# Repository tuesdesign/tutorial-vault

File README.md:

# Ontario Tech University Tutorial Slide Content

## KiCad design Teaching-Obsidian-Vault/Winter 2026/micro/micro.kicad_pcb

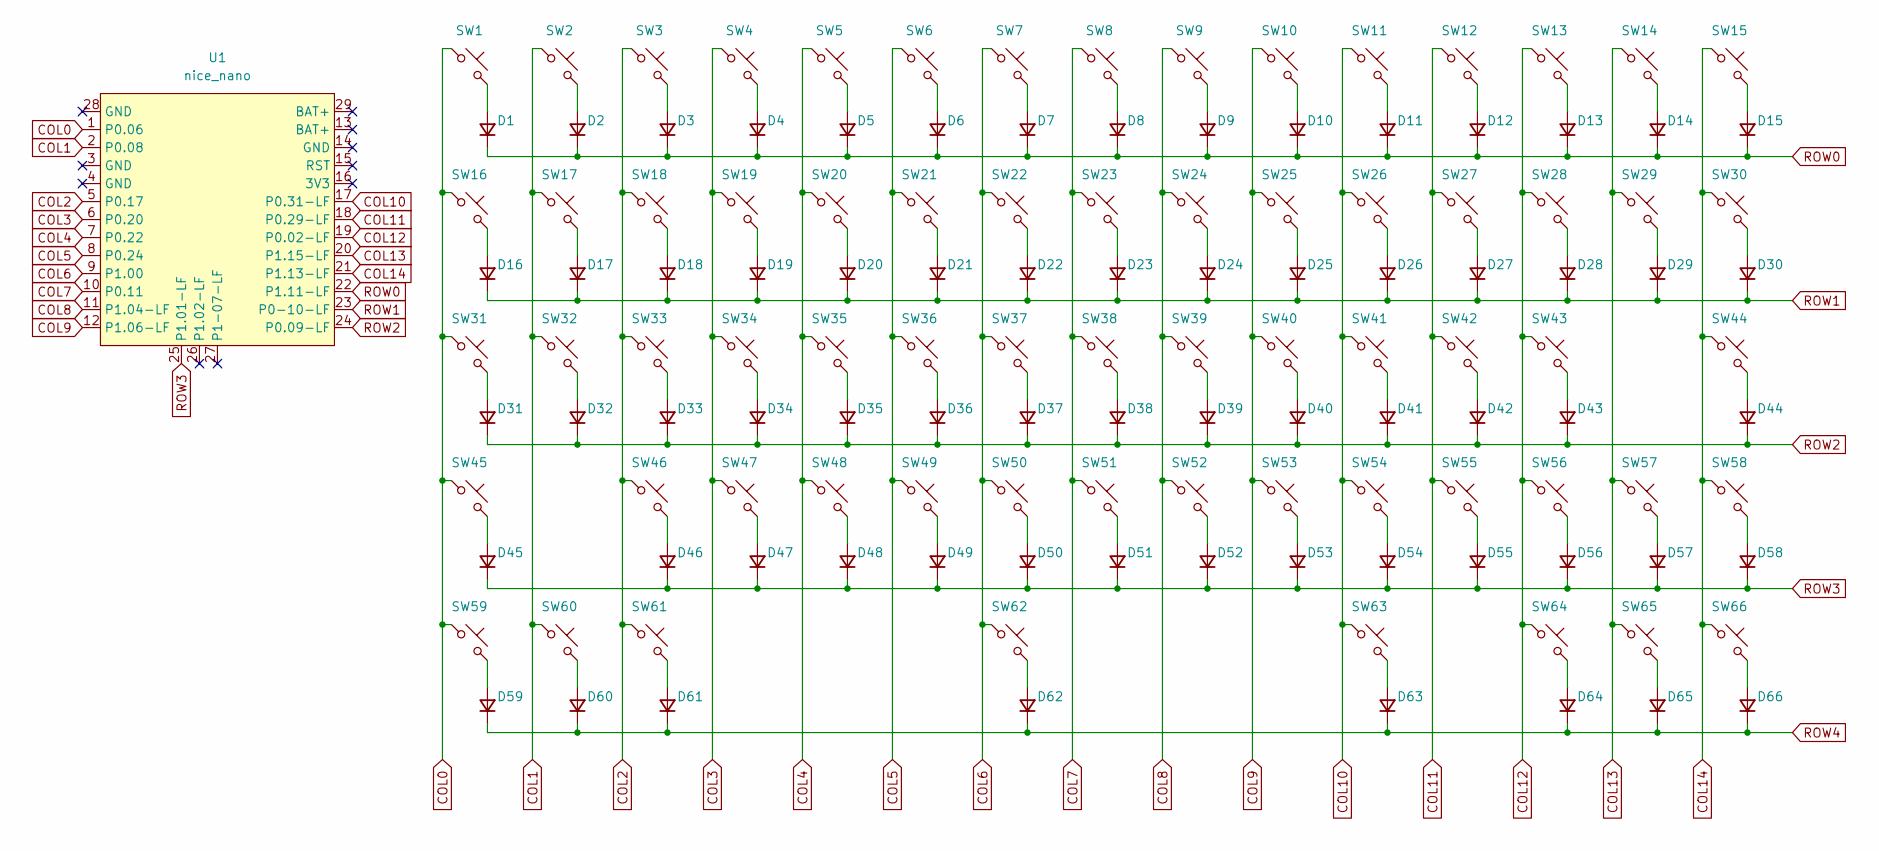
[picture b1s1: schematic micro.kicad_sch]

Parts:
D1, D2, D3, D4, D5, D6, D7, D8, D9, D10, D11, D12, D13, D14, D15, D16, D17, D18, D19, D20, D21, D22, D23, D24, D25, D26, D27, D28, D29, D30, D31, D32, D33, D34, D35, D36, D37, D38, D39, D40, D41, D42, D43, D44, D45, D46, D47, D48, D49, D50, D51, D52, D53, D54, D55, D56, D57, D58, D59, D60, D61, D62, D63, D64, D65, D66: D; D_SOD-123
SW1, SW2, SW3, SW4, SW5, SW6, SW7, SW8, SW9, SW10, SW11, SW12, SW13, SW14, SW17, SW18, SW19, SW20, SW21, SW22, SW23, SW24, SW25, SW26, SW27, SW28, SW30, SW32, SW33, SW34, SW35, SW36, SW37, SW38, SW39, SW40, SW41, SW42, SW43, SW44, SW46, SW47, SW48, SW49, SW50, SW51, SW52, SW53, SW54, SW55, SW56, SW58: SW_Push; SW_Hotswap_Kailh_Choc_V1V2_1.00u
SW15: SW_Push; SW_Hotswap_Kailh_Choc_V1V2_2.00u
SW16, SW63: SW_Push; SW_Hotswap_Kailh_Choc_V1V2_1.50u
SW29: SW_Push; SW_Hotswap_Kailh_Choc_V1_ISOEnter_90deg
SW31: SW_Push; SW_Hotswap_Kailh_Choc_V1V2_1.75u
SW45: SW_Push; SW_Hotswap_Kailh_Choc_V1V2_2.25u
SW57, SW59, SW60, SW61, SW64, SW65, SW66: SW_Push; SW_Hotswap_Kailh_Choc_V1V2_1.25u
SW62: SW_Push; SW_Hotswap_Kailh_Choc_V1V2_6.25u
U1: nice_nano; nice_nano_AH_USBup

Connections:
COL0: SW1.1, SW16.1, SW31.1, SW45.1, SW59.1, U1.1 (P0.06)
COL1: SW2.1, SW17.1, SW32.1, SW60.1, U1.2 (P0.08)
COL2: SW3.1, SW18.1, SW33.1, SW46.1, SW61.1, U1.5 (P0.17)
COL3: SW4.1, SW19.1, SW34.1, SW47.1, U1.6 (P0.20)
COL4: SW5.1, SW20.1, SW35.1, SW48.1, U1.7 (P0.22)
COL5: SW6.1, SW21.1, SW36.1, SW49.1, U1.8 (P0.24)
COL6: SW7.1, SW22.1, SW37.1, SW50.1, SW62.1, U1.9 (P1.00); also elsewhere on the board
COL7: SW8.1, SW23.1, SW38.1, SW51.1, U1.10 (P0.11)
COL8: SW9.1, SW24.1, SW39.1, SW52.1, U1.11 (P1.04-LF)
COL9: SW10.1, SW25.1, SW40.1, SW53.1, U1.12 (P1.06-LF)
COL10: SW11.1, SW26.1, SW41.1, SW54.1, SW63.1, U1.17 (P0.31-LF)
COL11: SW12.1, SW27.1, SW42.1, SW55.1, U1.18 (P0.29-LF)
COL12: SW13.1, SW28.1, SW43.1, SW56.1, SW64.1, U1.19 (P0.02-LF)
COL13: SW14.1, SW29.1, SW57.1, SW65.1, U1.20 (P1.15-LF)
COL14: SW15.1, SW30.1, SW44.1, SW58.1, SW66.1, U1.21 (P1.13-LF)
unnamed: D1.2 (A), SW1.2
unnamed: D2.2 (A), SW2.2
unnamed: D3.2 (A), SW3.2
unnamed: D4.2 (A), SW4.2
unnamed: D5.2 (A), SW5.2
unnamed: D6.2 (A), SW6.2
unnamed: D7.2 (A), SW7.2
unnamed: D8.2 (A), SW8.2
unnamed: D9.2 (A), SW9.2
unnamed: D10.2 (A), SW10.2
unnamed: D11.2 (A), SW11.2
unnamed: D12.2 (A), SW12.2
unnamed: D13.2 (A), SW13.2
unnamed: D14.2 (A), SW14.2
unnamed: D15.2 (A), SW15.2
unnamed: D16.2 (A), SW16.2
unnamed: D17.2 (A), SW17.2
unnamed: D18.2 (A), SW18.2
unnamed: D19.2 (A), SW19.2
unnamed: D20.2 (A), SW20.2
unnamed: D21.2 (A), SW21.2
unnamed: D22.2 (A), SW22.2
unnamed: D23.2 (A), SW23.2
unnamed: D24.2 (A), SW24.2
unnamed: D25.2 (A), SW25.2
unnamed: D26.2 (A), SW26.2
unnamed: D27.2 (A), SW27.2
unnamed: D28.2 (A), SW28.2
unnamed: D29.2 (A), SW29.2
unnamed: D30.2 (A), SW30.2
unnamed: D31.2 (A), SW31.2
unnamed: D32.2 (A), SW32.2
unnamed: D33.2 (A), SW33.2
unnamed: D34.2 (A), SW34.2
unnamed: D35.2 (A), SW35.2
unnamed: D36.2 (A), SW36.2
unnamed: D37.2 (A), SW37.2
unnamed: D38.2 (A), SW38.2
unnamed: D39.2 (A), SW39.2
unnamed: D40.2 (A), SW40.2
unnamed: D41.2 (A), SW41.2
unnamed: D42.2 (A), SW42.2
unnamed: D43.2 (A), SW43.2
unnamed: D44.2 (A), SW44.2
unnamed: D45.2 (A), SW45.2
unnamed: D46.2 (A), SW46.2
unnamed: D47.2 (A), SW47.2
unnamed: D48.2 (A), SW48.2
unnamed: D49.2 (A), SW49.2
unnamed: D50.2 (A), SW50.2
unnamed: D51.2 (A), SW51.2
unnamed: D52.2 (A), SW52.2
unnamed: D53.2 (A), SW53.2
unnamed: D54.2 (A), SW54.2
unnamed: D55.2 (A), SW55.2
unnamed: D56.2 (A), SW56.2
unnamed: D57.2 (A), SW57.2
unnamed: D58.2 (A), SW58.2
unnamed: D59.2 (A), SW59.2
unnamed: D60.2 (A), SW60.2
unnamed: D61.2 (A), SW61.2
unnamed 76: D62.2 (A), SW62.2; also elsewhere on the board
unnamed: D63.2 (A), SW63.2
unnamed: D64.2 (A), SW64.2
unnamed: D65.2 (A), SW65.2
unnamed: D66.2 (A), SW66.2
ROW0: D1.1 (K), D2.1 (K), D3.1 (K), D4.1 (K), D5.1 (K), D6.1 (K), D7.1 (K), D8.1 (K), D9.1 (K), D10.1 (K), D11.1 (K), D12.1 (K), D13.1 (K), D14.1 (K), D15.1 (K), U1.22 (P1.11-LF)
ROW1: D16.1 (K), D17.1 (K), D18.1 (K), D19.1 (K), D20.1 (K), D21.1 (K), D22.1 (K), D23.1 (K), D24.1 (K), D25.1 (K), D26.1 (K), D27.1 (K), D28.1 (K), D29.1 (K), D30.1 (K), U1.23 (P0-10-LF)
ROW2: D31.1 (K), D32.1 (K), D33.1 (K), D34.1 (K), D35.1 (K), D36.1 (K), D37.1 (K), D38.1 (K), D39.1 (K), D40.1 (K), D41.1 (K), D42.1 (K), D43.1 (K), D44.1 (K), U1.24 (P0.09-LF)
ROW3: D45.1 (K), D46.1 (K), D47.1 (K), D48.1 (K), D49.1 (K), D50.1 (K), D51.1 (K), D52.1 (K), D53.1 (K), D54.1 (K), D55.1 (K), D56.1 (K), D57.1 (K), D58.1 (K), U1.25 (P1.01-LF)
ROW4: D59.1 (K), D60.1 (K), D61.1 (K), D62.1 (K), D63.1 (K), D64.1 (K), D65.1 (K), D66.1 (K)

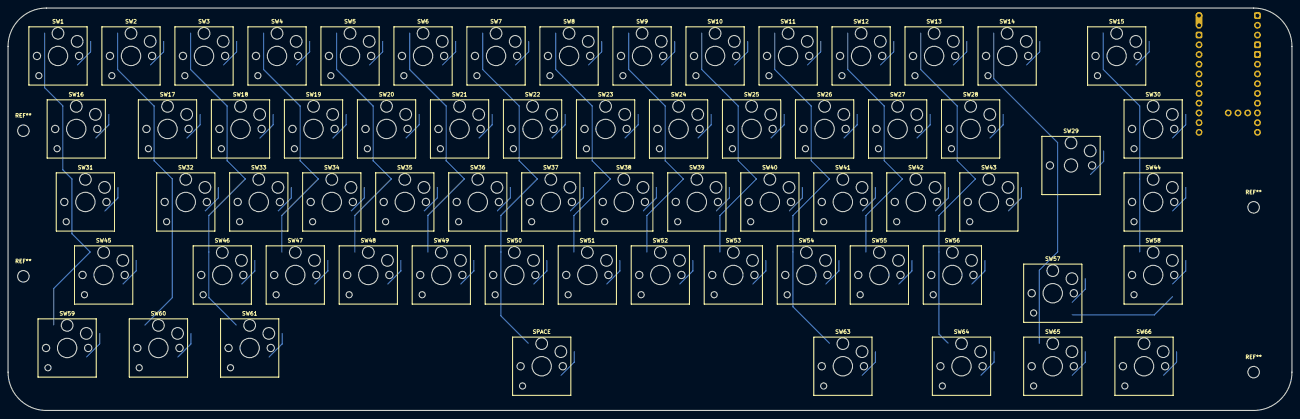
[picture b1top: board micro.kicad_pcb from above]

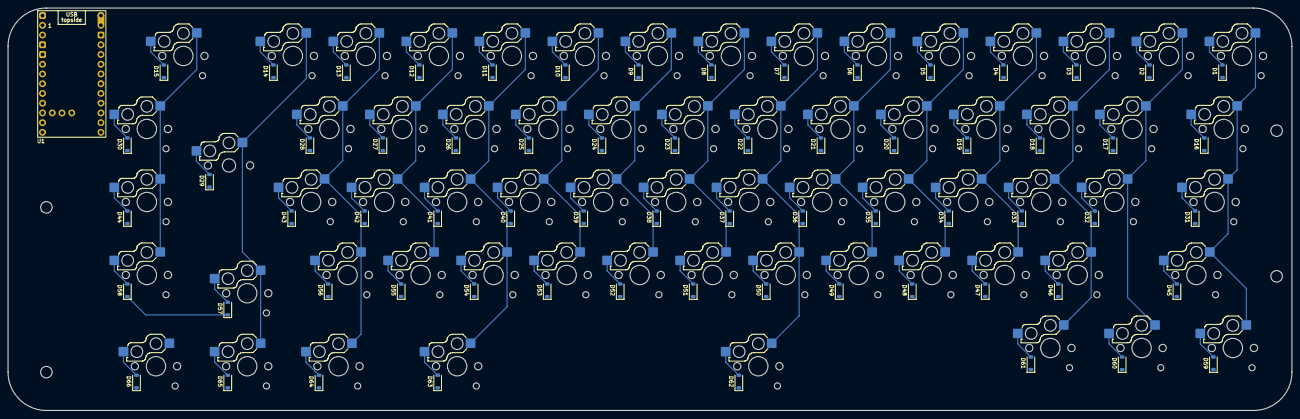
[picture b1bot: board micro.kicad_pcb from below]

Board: 2 copper layers, 335.0 x 105.0 mm, 133 parts (67 on the bottom side), 86 nets.

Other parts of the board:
SPACE: SW_Push; SW_Hotswap_Kailh_Choc_V1V2_6.25u

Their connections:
COL6: SPACE.1; also elsewhere on the board
unnamed 76: SPACE.2; also elsewhere on the board

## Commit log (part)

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2025-09-11 added sound week 2 tutorials
2025-09-12 Added GED Week 2 tutorial
2025-09-12 added title
2025-09-18 added gs w3
2025-09-19 Added GED W3
2025-09-25 Added Game Sound W4
2025-09-25 update GSW4 mini topic
2025-09-26 Added GED Week 4
2025-10-02 added gs w5
2025-10-03 added ged w5
2025-10-09 added gs w6
2025-10-10 added ged w6
2025-10-23 added gs w 8
2025-10-24 egtwz
2025-10-30 gfasdfgeqrwgftsdgf
2025-10-31 yuvgbctr
2025-11-06 add gs w10
2025-11-07 Added GED W10
2025-11-13 add gs w11
2025-11-21 added ged w11
2025-11-27 gfchetr
    anything
2026-01-19 updated for winter 26
2026-01-22 added ghd w1
2026-02-02 added icg w3
2026-02-05 added vlkjhbdfsghjgklfdashgjklafshdljk
2026-02-09 added cg w 4
2026-02-12 add hardware w4
2026-02-23 added gsw6
2026-02-25 stuff and things
2026-02-25 added ai lecture
2026-02-26 added ghw6
2026-03-12 added ghd w8
2026-03-19 added ghd w9
2026-03-23 added cg w10
2026-03-26 added ghw10
2026-04-01 yyytruyryutre
2026-06-13 moved and added pres
